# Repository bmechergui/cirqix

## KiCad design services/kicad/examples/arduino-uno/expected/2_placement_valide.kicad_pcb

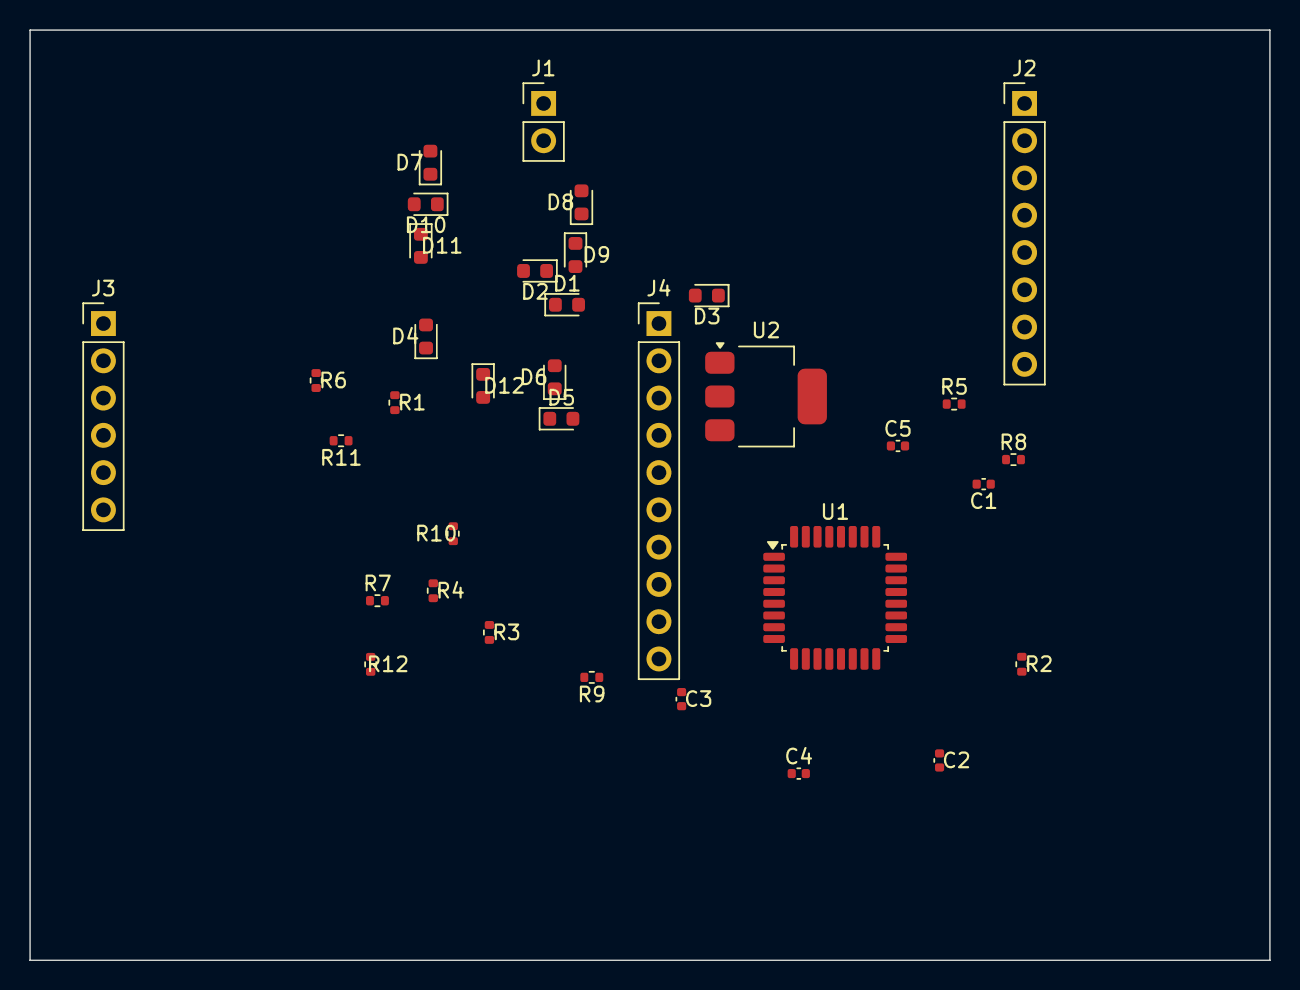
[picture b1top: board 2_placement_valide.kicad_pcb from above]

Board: 2 copper layers, 84.5 x 63.4 mm, 35 parts (0 on the bottom side), 16 nets, no tracks yet.

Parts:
C1, C2, C3, C4, C5: 100nF; C_0402_1005Metric
D1, D2, D3, D4, D5, D6, D7, D8, D9, D10, D11, D12: LED; LED_0603_1608Metric
J1: 5V; PinHeader_1x02_P2.54mm_Vertical
J2: POWER; PinHeader_1x08_P2.54mm_Vertical
J3: ANALOG; PinHeader_1x06_P2.54mm_Vertical
J4: DIGITAL; PinHeader_1x10_P2.54mm_Vertical
R1, R2, R3, R4, R5, R6, R7, R8, R9, R10, R11, R12: 330; R_0402_1005Metric
U1: ATmega328P-AU; TQFP-32_7x7mm_P0.8mm
U2: AMS1117-3.3; SOT-223-3_TabPin2

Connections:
+3V3: C1.1, C2.1, C3.1, C4.1, C5.1, J2.2, J3.2, J4.2, U1.1, U2.2
GND: C1.2, C2.2, C3.2, C4.2, C5.2, D1.2, D2.2, D3.2, D4.2, D5.2, D6.2, D7.2, D8.2, D9.2, D10.2, D11.2, D12.2, J1.2, J2.1, J3.1, J4.1, U2.1
LED1: D1.1, R1.2
LED2: D2.1, R2.2
LED3: D3.1, R3.2
LED5: D4.1, R4.2
LED6: D5.1, R5.2
LED7: D6.1, R6.2
LED9: D7.1, R7.2
LED10: D8.1, R8.2
LED11: D9.1, R9.2
LED13: D10.1, R10.2
LED14: D11.1, R11.2
LED15: D12.1, R12.2
POWER_3: J2.3, U1.2
VIN: J1.1, U2.3

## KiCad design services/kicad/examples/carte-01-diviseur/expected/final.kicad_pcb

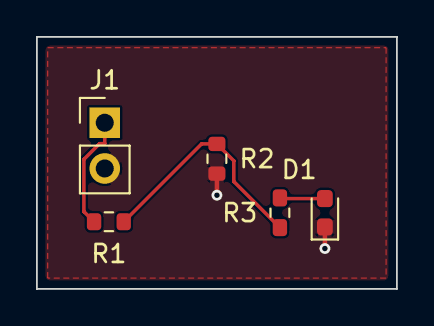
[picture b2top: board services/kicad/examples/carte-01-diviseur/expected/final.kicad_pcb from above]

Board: 2 copper layers, 20.0 x 14.0 mm, 5 parts (0 on the bottom side), 4 nets.

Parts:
D1: LED; LED_0603_1608Metric
J1: IN; PinHeader_1x02_P2.54mm_Vertical
R1, R2: 10k; R_0603_1608Metric
R3: 1k; R_0603_1608Metric

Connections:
GND: D1.1, J1.2, R2.2
LED_A: D1.2, R3.2
MID: R1.2, R2.1, R3.1
VIN: J1.1, R1.1

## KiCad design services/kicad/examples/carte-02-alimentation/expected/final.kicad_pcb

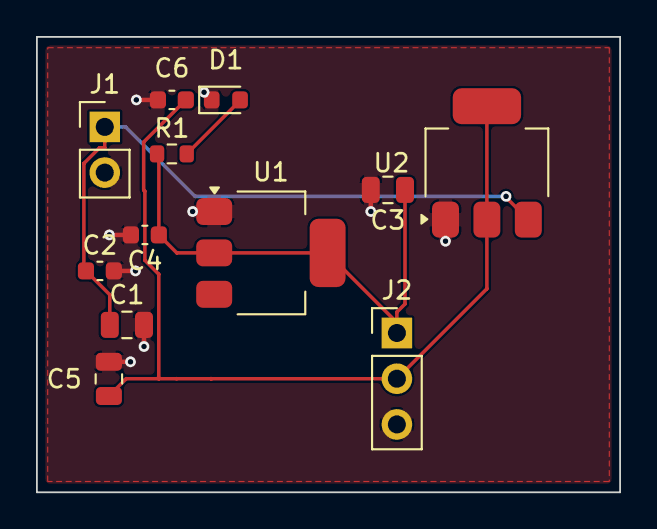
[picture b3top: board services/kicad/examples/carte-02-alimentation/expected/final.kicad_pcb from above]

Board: 2 copper layers, 32.4 x 25.3 mm, 12 parts (0 on the bottom side), 5 nets.

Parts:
C1, C3, C5: 10uF; C_0805_2012Metric
C2, C4, C6: 100nF; C_0603_1608Metric
D1: PWR_3V3; LED_0603_1608Metric
J1: IN_5V; PinHeader_1x02_P2.54mm_Vertical
J2: OUT; PinHeader_1x03_P2.54mm_Vertical
R1: 1k; R_0603_1608Metric
U1: AMS1117-3.3; SOT-223-3_TabPin2
U2: AMS1117-1.8; SOT-223-3_TabPin2

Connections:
+1V8: C5.1, C6.1, J2.2, U2.2
+3V3: C3.1, C4.1, J2.1, R1.1, U1.2
GND: C1.2, C2.2, C3.2, C4.2, C5.2, C6.2, D1.1, J1.2, J2.3, U1.1, U2.1
LED_A: D1.2, R1.2
VIN: C1.1, C2.1, J1.1, U2.3

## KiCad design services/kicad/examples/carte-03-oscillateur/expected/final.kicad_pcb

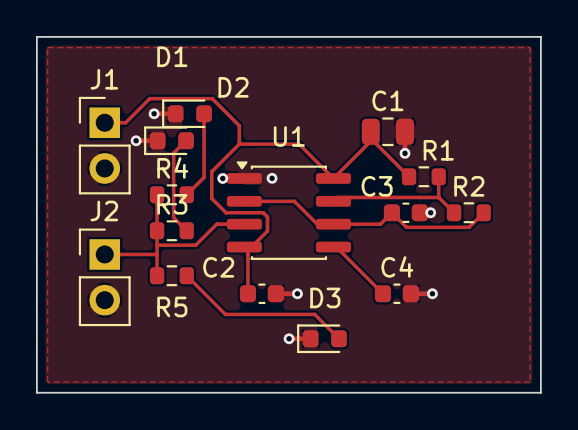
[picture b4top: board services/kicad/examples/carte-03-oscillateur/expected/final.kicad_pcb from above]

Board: 2 copper layers, 28.0 x 19.8 mm, 15 parts (0 on the bottom side), 9 nets.

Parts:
C1: 10uF; C_0805_2012Metric
C2: 100nF; C_0603_1608Metric
C3: 1uF; C_0603_1608Metric
C4: 10nF; C_0603_1608Metric
D1: OUT1; LED_0603_1608Metric
D2: OUT2; LED_0603_1608Metric
D3: OUT3; LED_0603_1608Metric
J1: PWR; PinHeader_1x02_P2.54mm_Vertical
J2: OUT; PinHeader_1x02_P2.54mm_Vertical
R1: 10k; R_0603_1608Metric
R2: 47k; R_0603_1608Metric
R3, R4, R5: 1k; R_0603_1608Metric
U1: NE555; SOIC-8_3.9x4.9mm_P1.27mm

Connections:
CTRL: C4.1, U1.5
DISCH: R1.2, R2.1, U1.7
GND: C1.2, C2.2, C3.2, C4.2, D1.1, D2.1, D3.1, J1.2, J2.2, U1.1
LED1_A: D1.2, R3.2
LED2_A: D2.2, R4.2
LED3_A: D3.2, R5.2
OUT: J2.1, R3.1, R4.1, R5.1, U1.3
THRES: C3.1, R2.2, U1.2, U1.6
VCC: C1.1, C2.1, J1.1, R1.1, U1.4, U1.8
